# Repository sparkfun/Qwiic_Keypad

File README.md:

SparkFun Qwiic KeyPad - 12 Button
========================================

[*SparkFun Qwiic Keypad - 12 Button (COM-15290)*](https://www.sparkfun.com/products/15290)

Keypads are very handy input devices, but who wants to tie up seven GPIO pins, wire up a handful of pull-up resistors, and write firmware that wastes valuable processing time scanning the keys for inputs? The SparkFun Qwiic Keypad comes fully assembled and makes the development process for adding a 12 button keypad easy. No voltage translation or figuring out which I2C pin is SDA or SCL, just plug and go! Utilizing our handy Qwiic system, no soldering is required to connect it to the rest of your system. However, we still have broken out 0.1"-spaced pins in case you prefer to use a breadboard.

Each of the keypad's 12 buttons has been labeled 1, 2, 3, 4, 5, 6, 7, 8, 9, 0, *, and # and has been formatted to into the same layout as a telephone keypad with each keypress resistance ranging between 10 and 150 Ohms. The Qwiic Keypad reads and stores the last 15 button presses in a First-In, First-Out (FIFO) stack, so you don’t need to constantly poll the keypad from your microcontroller. This information, then, is accessible through the Qwiic interface. The SparkFun Qwiic Keypad even has a software configurable I2C address so you can have multiple I2C devices on the same bus.

Repository Contents
-------------------

* **/Firmware** - The core sketch that runs Qwiic Keypad
* **/Hardware** - Eagle design files (.brd, .sch)

Documentation
--------------
* **[Hookup Guide](https://learn.sparkfun.com/tutorials/qwiic-keypad-hookup-guide)** - Hookup Guide for the SparkFun Qwiic Keypad - 12 Button
* **[Product Showcase - YouTube Video](https://youtu.be/QPRrk0tHk08)** - Product showcase video with Rob Reynolds introducing the product and showing a few examples.
* **[Library](https://github.com/sparkfun/SparkFun_Qwiic_Keypad_Arduino_Library)** - Arduino library for the SparkFun Qwiic Keypad - 12 Button
* **[Installing an Arduino Library](https://learn.sparkfun.com/tutorials/installing-an-arduino-library/)** - Basic instructions on installing an Arduino library

Product Versions
--------------
* [COM-15290](https://www.sparkfun.com/products/15290) - SparkFun version
* [SPX-14836](https://www.sparkfun.com/products/retired/14836) - SparkX version

License Information
-------------------

This product is _**open source**_! 

Please review the LICENSE.md file for license information.

If you have any questions or concerns on licensing, please contact technical support on our [SparkFun forums](https://forum.sparkfun.com/viewforum.php?f=152).

Please use, reuse, and modify these files as you see fit. Please maintain attribution to SparkFun Electronics and release under the same license.

Distributed as-is; no warranty is given.

- Your friends at SparkFun.

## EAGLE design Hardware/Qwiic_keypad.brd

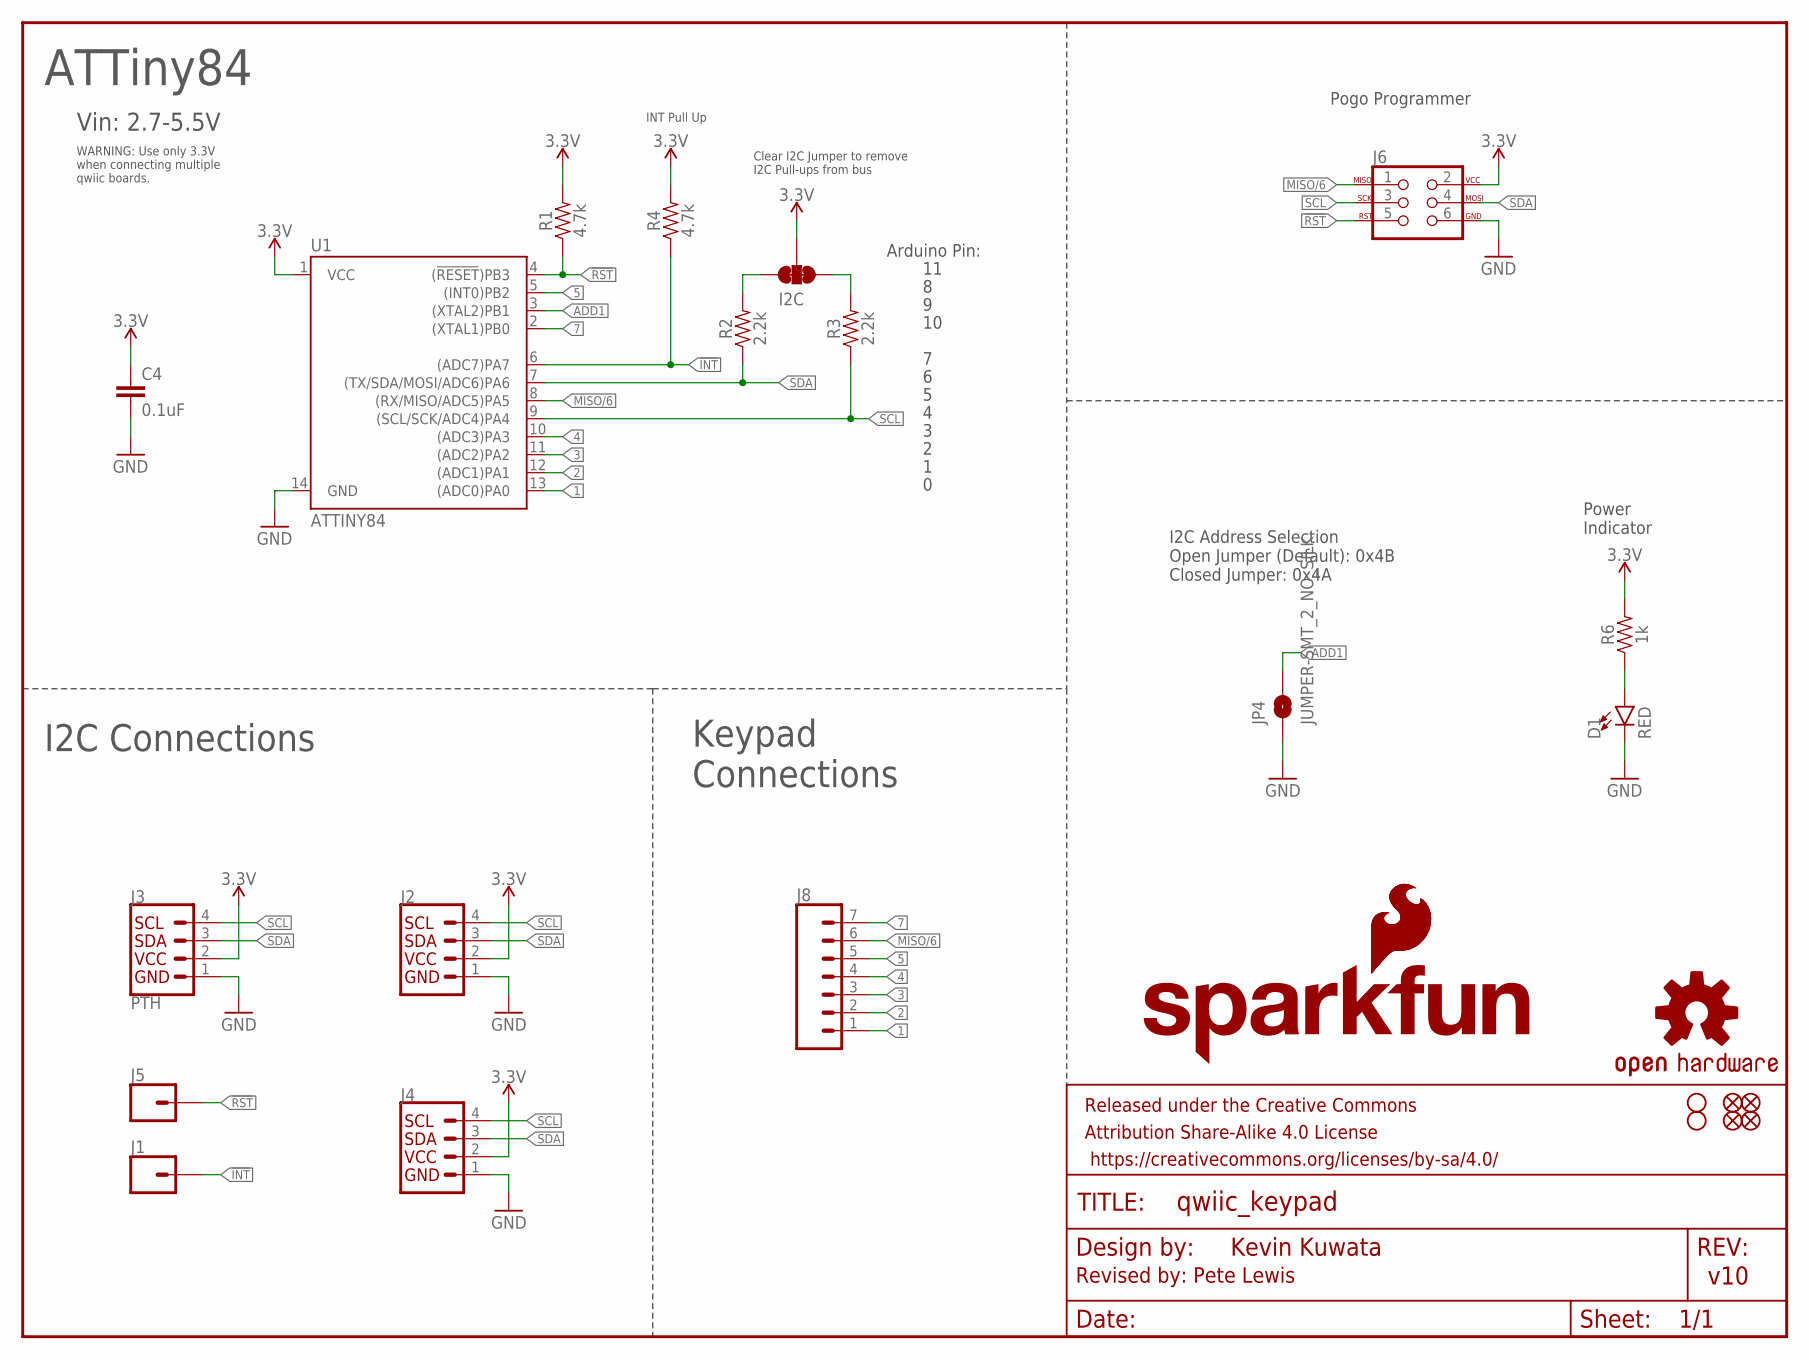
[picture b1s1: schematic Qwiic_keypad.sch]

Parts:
C4: 0.1uF; 0603
D1: RED; LED-0603
FRAME1: FRAME-LETTER; CREATIVE_COMMONS
H1, H2: STAND-OFF
I2C: JUMPER-SMT_3_2-NC_TRACE_SILK; SMT-JUMPER_3_2-NC_TRACE_SILK
J1, J5: CONN_01PTH_NO_SILK_YES_STOP; 1X01_NO_SILK
J2, J4: QWIIC_CONNECTORJS-1MM; JST04_1MM_RA
J3: PTH; 1X04_NO_SILK
J6: AVR_SPI_PROG_3X2TESTPOINTS; 2X3_TEST_POINTS
J8: CONN_07LOCK_NO_SILK; 1X07_LOCK_NO_SILK
JP1, JP2, JP3, JP6: FIDUCIALUFIDUCIAL; MICRO-FIDUCIAL
JP4: JUMPER-SMT_2_NO_SILK; SMT-JUMPER_2_NO_SILK
LOGO1: OSHW-LOGOMINI; OSHW-LOGO-MINI
LOGO2: SFE_LOGO_NAME_FLAME.1_INCH; SFE_LOGO_NAME_FLAME_.1
LOGO3: SFE_LOGO_FLAME.2_INCH; SFE_LOGO_FLAME_.2
R1, R4: 4.7k; 0603
R2, R3: 2.2k; 0603
R6: 1k; 0603
U1: ATTINY84; SO14

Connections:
1: J8.1, U1.13 ((ADC0)PA0)
2: J8.2, U1.12 ((ADC1)PA1)
3: J8.3, U1.11 ((ADC2)PA2)
3.3V: C4.1, I2C.2, J2.2, J3.2, J4.2, J6.2, R1.2, R4.2, R6.2, U1.1 (VCC)
4: J8.4, U1.10 ((ADC3)PA3)
5: J8.5, U1.5 ((INT0)PB2)
7: J8.7, U1.2 ((XTAL1)PB0)
!INT: J1.1, R4.1, U1.6 ((ADC7)PA7)
!RST: J5.1, J6.5, R1.1, U1.4 ((!RESET!)PB3)
ADD1: JP4.2, U1.3 ((XTAL2)PB1)
GND: C4.2, D1.C, J2.1, J3.1, J4.1, J6.6, JP4.1, U1.14 (GND)
MISO/6: J6.1, J8.6, U1.8 ((RX/MISO/ADC5)PA5)
unnamed: D1.A, R6.1
unnamed: I2C.3, R2.2
unnamed: I2C.1, R3.2
SCL: J2.4, J3.4, J4.4, J6.3, R3.1, U1.9 ((SCL/SCK/ADC4)PA4)
SDA: J2.3, J3.3, J4.3, J6.4, R2.1, U1.7 ((TX/SDA/MOSI/ADC6)PA6)

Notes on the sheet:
Kevin Kuwata
v10
I2C Address Selection Open Jumper (Default): 0x4B Closed Jumper: 0x4A
Power Indicator
Arduino Pin:
Revised by: Pete Lewis
INT Pull Up
Clear I2C Jumper to remove I2C Pull-ups from bus
ATTiny84
I2C Connections
Pogo Programmer
Vin: 2.7-5.5V
Keypad Connections
WARNING: Use only 3.3V when connecting multiple qwiic boards.

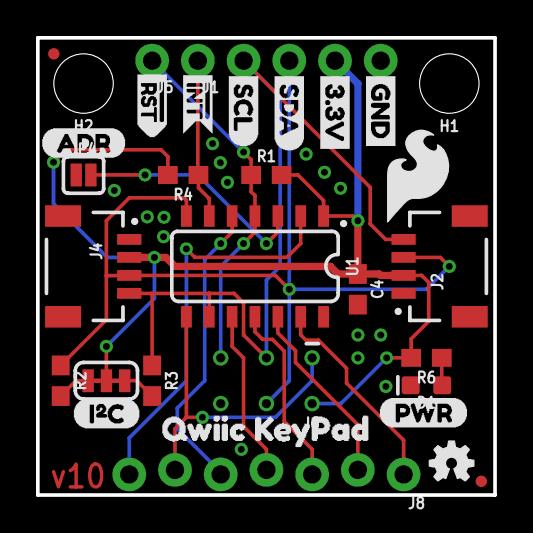
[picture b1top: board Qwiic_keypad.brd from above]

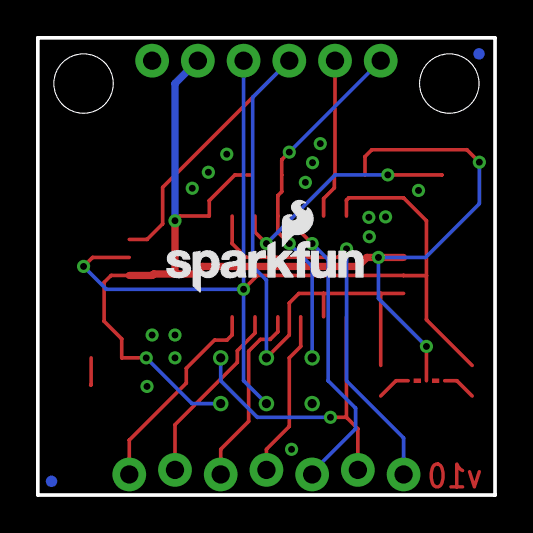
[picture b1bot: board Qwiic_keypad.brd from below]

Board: 2 copper layers, 25.4 x 25.4 mm, 37 parts (3 on the bottom side), 17 nets.

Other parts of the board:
U$3: 3.3V
U$4: GND
U$5: SDA
U$6: SCL
U$8: (PWR)
U$9: (I_SUPER2_C)
U$10: (ADR)
U$11: #RST>
U$12: #INT1
U$15: QWIIC_KEYPAD0

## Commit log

2019-02-28 copying over sparkX repo
    note, not including hardware production panel files, those will need to be recreated anyways with this new revision.
2019-02-28 updating hardware
    -SFE logo in schematic (w/ slight re-arrange to fit)
    -changed version in sch (and brd) to v10
    -bumped traces up from 6 mils to 8 mils.
    -bumped vias up from 12 mils to 15 mils.
    -switched to "sfe tight" drc
    -minor trace nudgeing to avoid clearance warnings.
2019-03-06 Locking footprint on 1x7 connector to keypad
    This will help with holding position during selective solder
2019-03-06 added INT pullup resistor
2019-03-07 hardware review changes
    beef up trace to 3.3V PTH header breakout as well.
    Nudged I2C label up to match power label hieght.
    ATTINY84 polarity mark fill in library
    Logo up to .2 size flame.
    Schematic note for I2C pullup jumper
    Updated ATTiny device (just the symbol changed, but needed to "replace" due to new pin names).
2019-03-07 double-check (my run) fixes
    added SS path on 48.
    package update on address jumper - to 8 mil width on silk outline.
    library update to SFE library on I2C jumper (was sparkx lbr).
    some minor routing tweaks to allow more gnd flow
2019-03-12 Fixed overflow issues
    Discovered a problem: If you didn't read the keypad for a long time, and the user had input more than 15 buttons, there was an overflow error.
    It had to do with the incrementing of oldest and newest press variables. The incrementations needed to be ahead of the read/write actions. We also needed some more conditionals to handle the "trailin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
    Also, started to add in the register map stuff.
2019-03-12 autoformatting corrections
2019-03-16 version number and "update fifo command bit" working
2019-03-16 update fifo and read button working
    also, more debug while devving on an Uno.
2019-03-17 removing old responseBuffer stuff, update comments
2019-03-18 I2C change working properly now
    It was not updating the I2C address (in the registerMap.i2cAddress) correctly in the readSystemSettings() function. Now it is.
    Also, removed the old (and now unused) variable "setting_i2c_address".
    Added some more debug at setup when devving on an Uno - EEPROM read, for sanity.
2019-03-18 correcting device name in #elif for pin definitions
    it is in fact an ATTiny84
2019-03-21 interrupt pin correction for FALLING detection
    When a new button is pressed, I added this:
    digitalWrite(interruptPin, HIGH); //Set Int HIGH, to cause a FALLING edge later
    //Note, this will be set LOW again at bottom of main loop.
    //This FALLING edge is useful for hardware INT on your project's master IC.
    With this, when a new button is pressed, it causes a falling edge on int. Great when using hardware interrupt on your controller IC.
2019-04-15 exported firmware hex file for production use
2019-04-25 Added license md file
2019-04-25 Updating Readme with proper live links and such
2019-04-25 removing old sparkX example sketches and programming
2019-04-29 Added library manager link (with search) to correct keypad library
    for easily finding the correct library you need to compile this firmware. Note, the search actually uses words that are unique to the library "sentence".
2022-02-23 Add check for non-zero numberOfBytesReceived
    ensure we received valid byte or bytes - note, an I2C scan does not send anything, so without this, it would overright registerNumber with Zero value.
2022-02-23 Formatting - adding tabs to inside of if statement

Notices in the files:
parts and their libraries:
SparkFun-Resistors: Licensing: Creative Commons ShareAlike 4.0 International - https://creativecommons.org/licenses/by-sa/4.0
SparkFun-Aesthetics: Released under the Creative Commons Attribution Share-Alike 4.0 License
SparkFun-Aesthetics: https://creativecommons.org/licenses/by-sa/4.0
